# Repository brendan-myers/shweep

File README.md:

# Shweep

A 58 key, low-profile, split, ortholinear(ish), keyboard for the XIAO nRF52840.

> [!NOTE]
> Everything required to build a Shweep is available here, but there is no build guide (yet). If you've done this sort of thing before then you shouldn't have any trouble, just note that D35 and D45 (likewise D40 and D50 for the RHS) point in the opposite direction to other diodes. Also, the MCU is flipped on the RHS board.

## Firmware

[ZMK firmware is available here](https://github.com/brendan-myers/shweep-shield-module)

## PCB

Most PCB fabs require a minimum order of 5 boards; this board is reversable so you can build both halves without having to place a different order for each.

## BOM (per side)

- 1x Seeed Studio
- 29x Kailh choc v1 switches
- 29x SOD-123 diodes
- (optional) 29x Kailh sockets (if you don't want to solder switches directly to the board)
- (optional) 2x 7x1 2.54m female headers (if you don't want to solder the MCU directly to the board).
- (optional) 1x [PCM12 SPDT](https://jlcpcb.com/partdetail/ck-PCM12SMTR/C221841) switch
- (optional) 1x [JST S2B-PH-SM4-TB](https://jlcpcb.com/partdetail/JST-S2B_PH_SM4_TB_LF_SN/C295747) battery socket

## Todos

- Build guide.
- (PCB) Use reversible footprint for Kailh sockets (instead of 2 overlapping single-sided footprints).
- (PCB) Fully connected diodes, ie allow diode for each key to be on either side of the board instead of forcing them to be on the same side as the Kailh sockets. This is cheaper to manufacture (PCBA is less expensive when components are only on one side).
- (PCB) Include through-hole diodes.
- (PCB) Investigate: charging battery without board being switched "on".

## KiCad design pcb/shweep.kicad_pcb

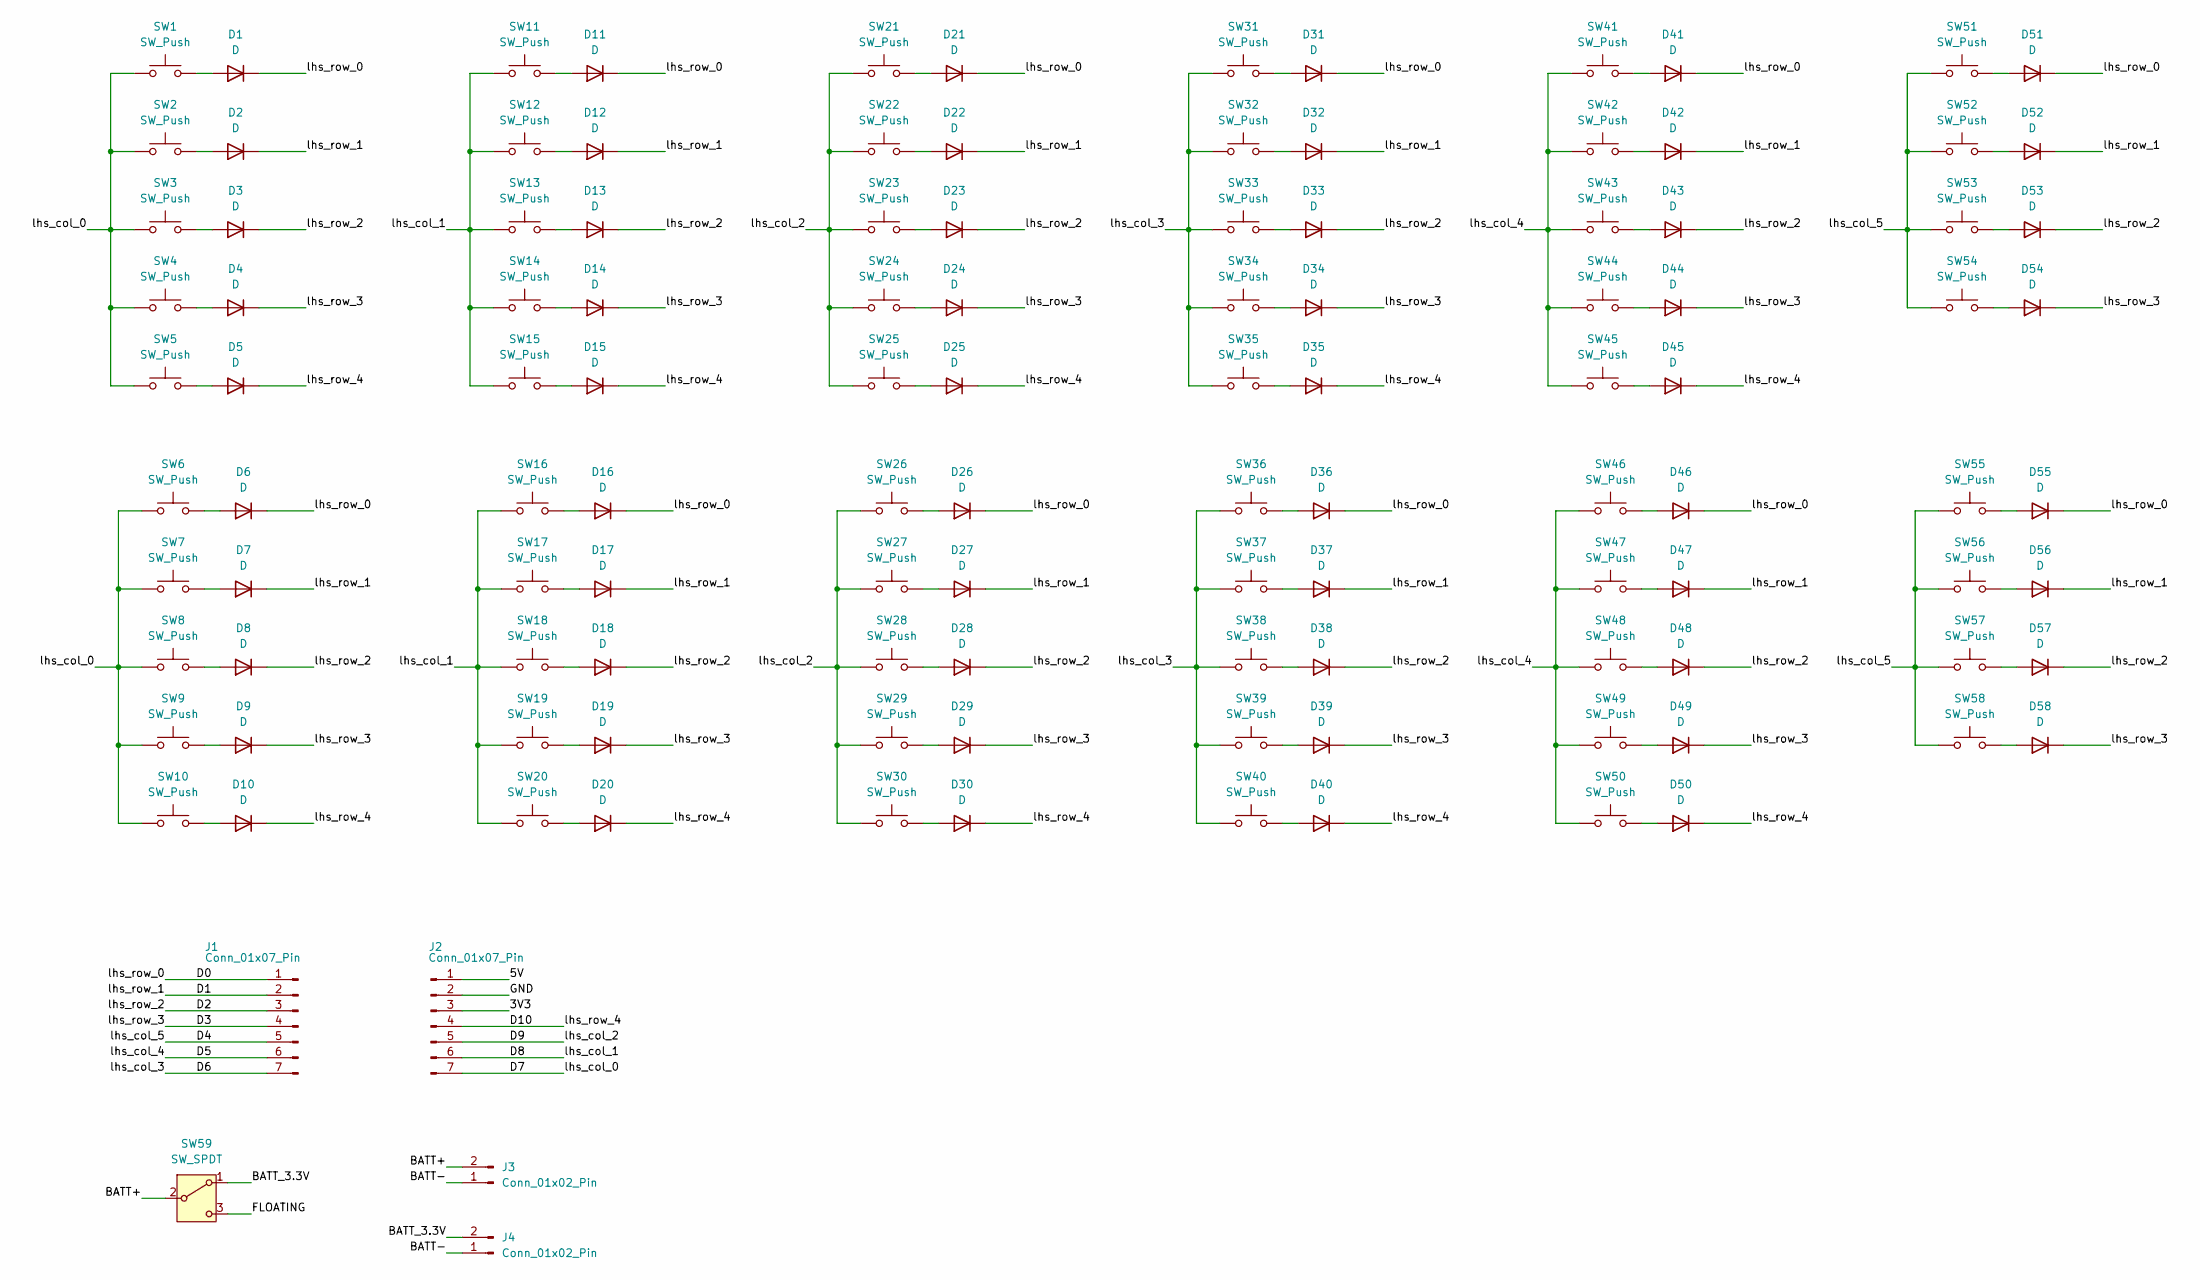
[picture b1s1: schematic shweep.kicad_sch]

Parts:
D1, D2, D3, D4, D5, D6, D7, D8, D9, D10, D11, D12, D13, D14, D15, D16, D17, D18, D19, D20, D21, D22, D23, D24, D25, D26, D27, D28, D29, D30, D31, D32, D33, D34, D35, D36, D37, D38, D39, D40, D41, D42, D43, D44, D45, D46, D47, D48, D49, D50, D51, D52, D53, D54, D55, D56, D57, D58: D; D_0805_2012Metric_Pad1.15x1.40mm_HandSolder
J1, J2: Conn_01x07_Pin; PinSocket_1x07_P2.54mm_Vertical
J3: Conn_01x02_Pin; Molex_CLIK-Mate_502386-0270_1x02-1MP_P1.25mm_Horizontal
J4: Conn_01x02_Pin; PinHeader_1x02_P1.27mm_Horizontal
SW1, SW2, SW3, SW4, SW5, SW6, SW7, SW8, SW9, SW10, SW11, SW12, SW13, SW14, SW15, SW16, SW17, SW18, SW19, SW20, SW21, SW22, SW23, SW24, SW25, SW26, SW27, SW28, SW29, SW30, SW31, SW32, SW33, SW34, SW35, SW36, SW37, SW38, SW39, SW40, SW41, SW42, SW43, SW44, SW45, SW46, SW47, SW48, SW49, SW50, SW51, SW52, SW53, SW54, SW55, SW56, SW57, SW58: SW_Push; Kailh_socket_PG1350
SW59: SW_SPDT; SW_SPDT_CK_JS102011SAQN

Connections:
/3V3: J2.3
/5V: J2.1
/BATT+: J3.2, SW59.2 (B); also elsewhere on the board
/BATT-: J3.1, J4.1; also elsewhere on the board
/BATT_3.3V: J4.2, SW59.1 (A); also elsewhere on the board
/D0: D1.1 (K), D6.1 (K), D11.1 (K), D16.1 (K), D21.1 (K), D26.1 (K), D31.1 (K), D36.1 (K), D41.1 (K), D46.1 (K), D51.1 (K), D55.1 (K), J1.1
/D1: D2.1 (K), D7.1 (K), D12.1 (K), D17.1 (K), D22.1 (K), D27.1 (K), D32.1 (K), D37.1 (K), D42.1 (K), D47.1 (K), D52.1 (K), D56.1 (K), J1.2
/D2: D3.1 (K), D8.1 (K), D13.1 (K), D18.1 (K), D23.1 (K), D28.1 (K), D33.1 (K), D38.1 (K), D43.1 (K), D48.1 (K), D53.1 (K), D57.1 (K), J1.3
/D3: D4.1 (K), D9.1 (K), D14.1 (K), D19.1 (K), D24.1 (K), D29.1 (K), D34.1 (K), D39.1 (K), D44.1 (K), D49.1 (K), D54.1 (K), D58.1 (K), J1.4
/D4: J1.5, SW51.1, SW52.1, SW53.1, SW54.1, SW55.1, SW56.1, SW57.1, SW58.1
/D5: J1.6, SW41.1, SW42.1, SW43.1, SW44.1, SW45.1, SW46.1, SW47.1, SW48.1, SW49.1, SW50.1
/D6: J1.7, SW31.1, SW32.1, SW33.1, SW34.1, SW35.1, SW36.1, SW37.1, SW38.1, SW39.1, SW40.1
/D7: J2.7, SW1.1, SW2.1, SW3.1, SW4.1, SW5.1, SW6.1, SW7.1, SW8.1, SW9.1, SW10.1
/D8: J2.6, SW11.1, SW12.1, SW13.1, SW14.1, SW15.1, SW16.1, SW17.1, SW18.1, SW19.1, SW20.1
/D9: J2.5, SW21.1, SW22.1, SW23.1, SW24.1, SW25.1, SW26.1, SW27.1, SW28.1, SW29.1, SW30.1
/D10: D5.1 (K), D10.1 (K), D15.1 (K), D20.1 (K), D25.1 (K), D30.1 (K), D35.1 (K), D40.1 (K), D45.1 (K), D50.1 (K), J2.4
/FLOATING: SW59.3 (C); also elsewhere on the board
/GND: J2.2
unnamed: D1.2 (A), SW1.2
unnamed: D2.2 (A), SW2.2
unnamed: D3.2 (A), SW3.2
unnamed: D4.2 (A), SW4.2
unnamed: D5.2 (A), SW5.2
unnamed: D6.2 (A), SW6.2
unnamed: D7.2 (A), SW7.2
unnamed: D8.2 (A), SW8.2
unnamed: D9.2 (A), SW9.2
unnamed: D10.2 (A), SW10.2
unnamed: D11.2 (A), SW11.2
unnamed: D12.2 (A), SW12.2
unnamed: D13.2 (A), SW13.2
unnamed: D14.2 (A), SW14.2
unnamed: D15.2 (A), SW15.2
unnamed: D16.2 (A), SW16.2
unnamed: D17.2 (A), SW17.2
unnamed: D18.2 (A), SW18.2
unnamed: D19.2 (A), SW19.2
unnamed: D20.2 (A), SW20.2
unnamed: D21.2 (A), SW21.2
unnamed: D22.2 (A), SW22.2
unnamed: D23.2 (A), SW23.2
unnamed: D24.2 (A), SW24.2
unnamed: D25.2 (A), SW25.2
unnamed: D26.2 (A), SW26.2
unnamed: D27.2 (A), SW27.2
unnamed: D28.2 (A), SW28.2
unnamed: D29.2 (A), SW29.2
unnamed: D30.2 (A), SW30.2
unnamed: D31.2 (A), SW31.2
unnamed: D32.2 (A), SW32.2
unnamed: D33.2 (A), SW33.2
unnamed: D34.2 (A), SW34.2
unnamed: D35.2 (A), SW35.2
unnamed: D36.2 (A), SW36.2
unnamed: D37.2 (A), SW37.2
unnamed: D38.2 (A), SW38.2
unnamed: D39.2 (A), SW39.2
unnamed: D40.2 (A), SW40.2
unnamed: D41.2 (A), SW41.2
unnamed: D42.2 (A), SW42.2
unnamed: D43.2 (A), SW43.2
unnamed: D44.2 (A), SW44.2
unnamed: D45.2 (A), SW45.2
unnamed: D46.2 (A), SW46.2
unnamed: D47.2 (A), SW47.2
unnamed: D48.2 (A), SW48.2
unnamed: D49.2 (A), SW49.2
unnamed: D50.2 (A), SW50.2
unnamed: D51.2 (A), SW51.2
unnamed: D52.2 (A), SW52.2
unnamed: D53.2 (A), SW53.2
unnamed: D54.2 (A), SW54.2
unnamed: D55.2 (A), SW55.2
unnamed: D56.2 (A), SW56.2
unnamed: D57.2 (A), SW57.2
unnamed: D58.2 (A), SW58.2

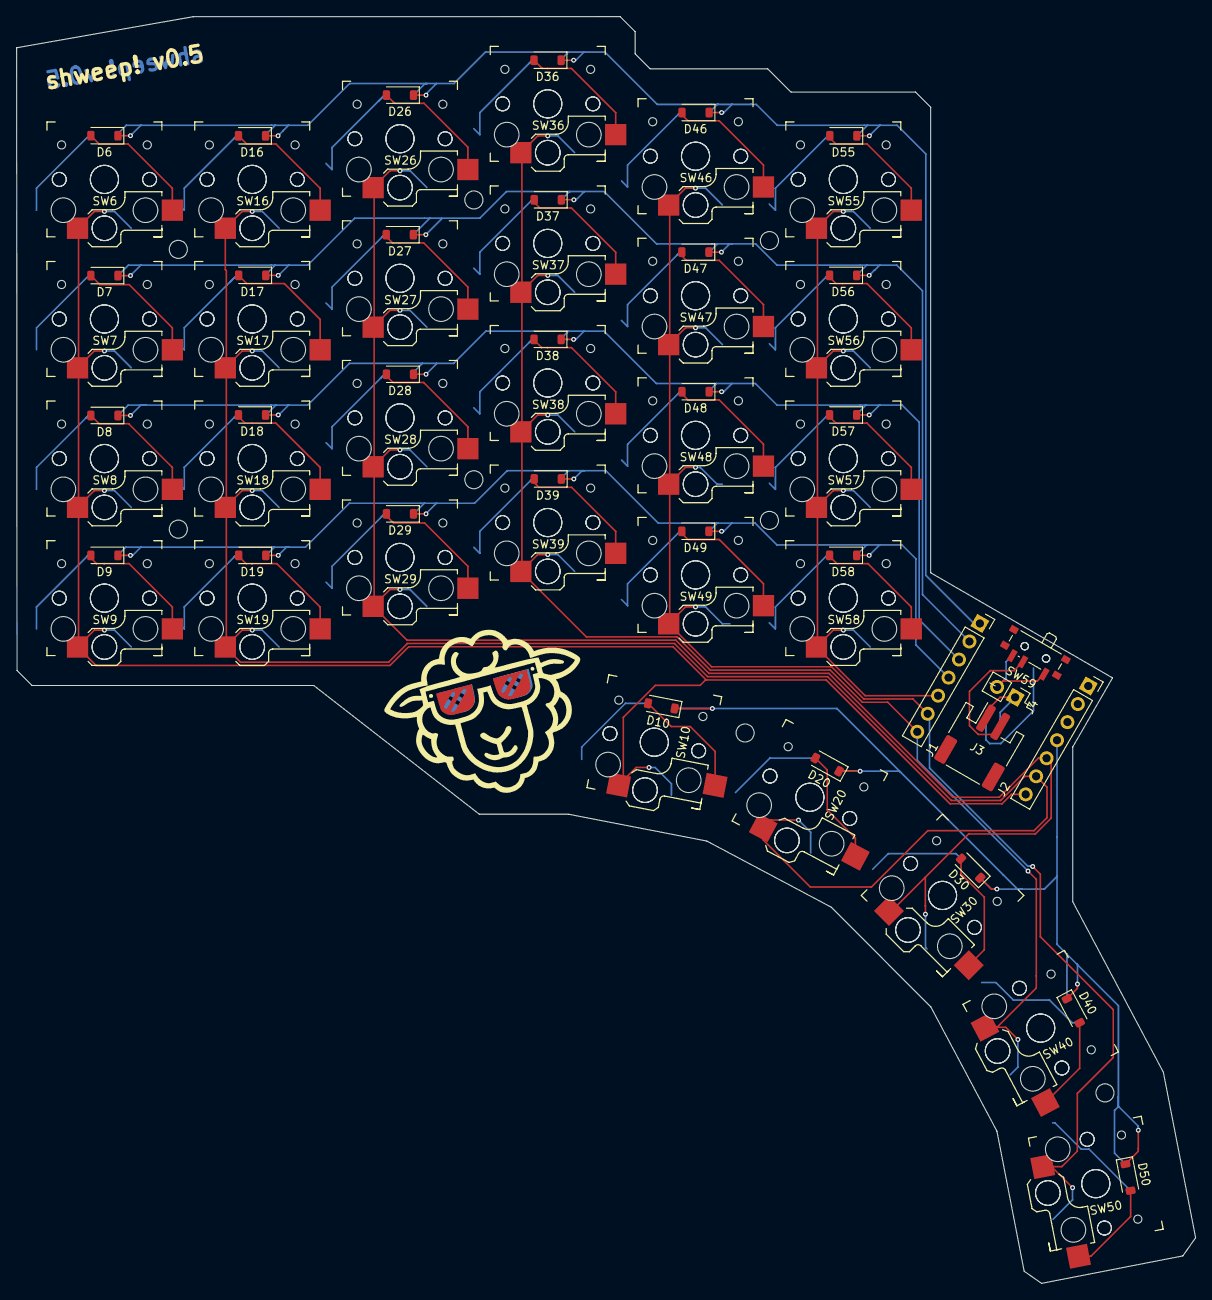
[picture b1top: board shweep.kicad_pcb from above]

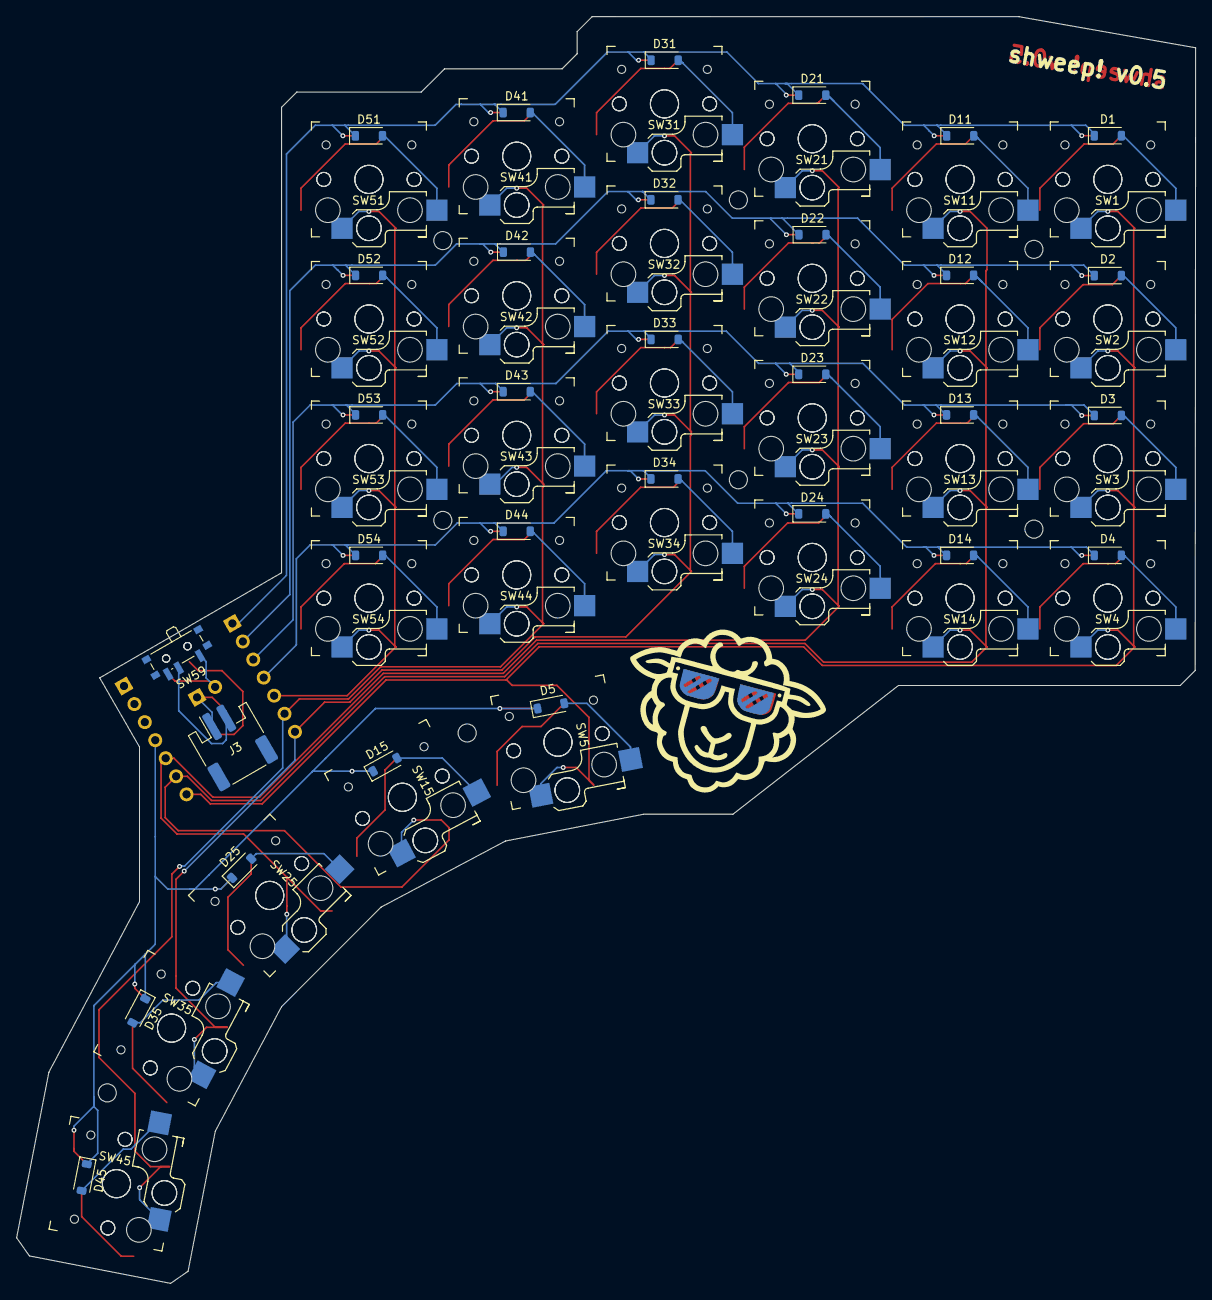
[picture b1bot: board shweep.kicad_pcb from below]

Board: 2 copper layers, 143.6 x 154.3 mm, 123 parts (60 on the bottom side), 73 nets.

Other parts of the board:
J3#2: Conn_01x02_Pin; JST_PH_S2B-PH-SM4-TB_1x02-1MP_P2.00mm_Horizontal
SW59#2: SW_SPDT; SW_SPDT_PCM12

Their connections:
/BATT+: J3#2.2, SW59#2.2 (B); also elsewhere on the board
/BATT-: J3#2.1; also elsewhere on the board
/BATT_3.3V: SW59#2.1 (A); also elsewhere on the board
/FLOATING: SW59#2.3 (C); also elsewhere on the board

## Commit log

2024-10-19 init
